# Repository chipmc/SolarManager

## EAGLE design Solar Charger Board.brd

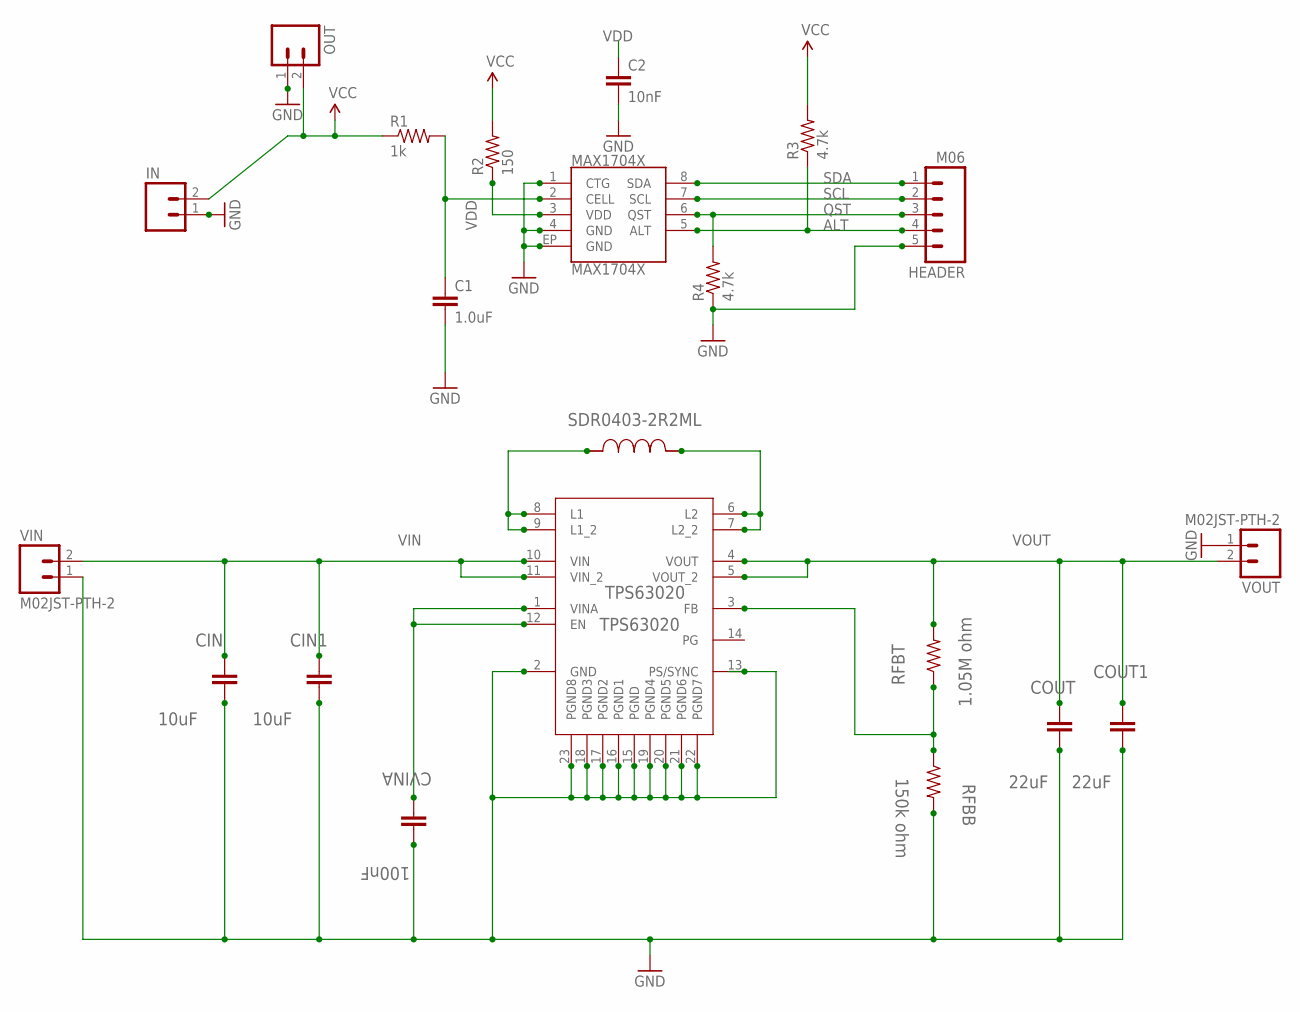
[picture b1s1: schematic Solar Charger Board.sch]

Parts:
C1: 1.0uF; 0805
C2: 10nF; 0805
CIN, CIN1: 10uF; 0805
COUT, COUT1: 22uF; 0805
CVINA: 100nF; 0805
HEADER: M06; 1X05
IN: input; JST-2-PTH
L1: SDR0403-2R2ML; SDR0403
MAX1704X: MAX1704X; TDFN-8
OUT: M02JST-PTH-2; JST-2-PTH
R1: 1k; 0805
R2: 150; 0805
R3, R4: 4.7k; 0805
RFBB: 150k ohm; 0805
RFBT: 1.05M ohm; 0805
TPS63020: TPS63020; QFN14-3X4MM
VIN: M02JST-PTH-2; JST-2-PTH
VOUT: M02JST-PTH-2; JST-2-PTH

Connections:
ALT: HEADER.4, MAX1704X.5 (ALT), R3.1
FB: RFBB.1, RFBT.1, TPS63020.3 (FB)
GND: C1.2, C2.2, CIN.2, CIN1.2, COUT.2, COUT1.2, CVINA.2, HEADER.5, IN.1, MAX1704X.1 (CTG), MAX1704X.4 (GND), MAX1704X.EP (GND), OUT.1, R4.1, RFBB.2, TPS63020.2 (GND), TPS63020.13 (PS/SYNC), TPS63020.15 (PGND), TPS63020.16 (PGND1), TPS63020.17 (PGND2), TPS63020.18 (PGND3), TPS63020.19 (PGND4), TPS63020.20 (PGND5), TPS63020.21 (PGND6), TPS63020.22 (PGND7), TPS63020.23 (PGND8), VIN.1, VOUT.1
unnamed: CVINA.1, TPS63020.1 (VINA), TPS63020.12 (EN)
unnamed: C1.1, MAX1704X.2 (CELL), R1.2
unnamed: L1.1, TPS63020.8 (L1), TPS63020.9 (L1_2)
unnamed: L1.2, TPS63020.6 (L2), TPS63020.7 (L2_2)
QST: HEADER.3, MAX1704X.6 (QST), R4.2
SCL: HEADER.2, MAX1704X.7 (SCL)
SDA: HEADER.1, MAX1704X.8 (SDA)
VCC: IN.2, OUT.2, R1.1, R2.2, R3.2
VDD: C2.1, MAX1704X.3 (VDD), R2.1
VIN: CIN.1, CIN1.1, TPS63020.10 (VIN), TPS63020.11 (VIN_2), VIN.2
VOUT: COUT.1, COUT1.1, RFBT.2, TPS63020.4 (VOUT), TPS63020.5 (VOUT_2), VOUT.2

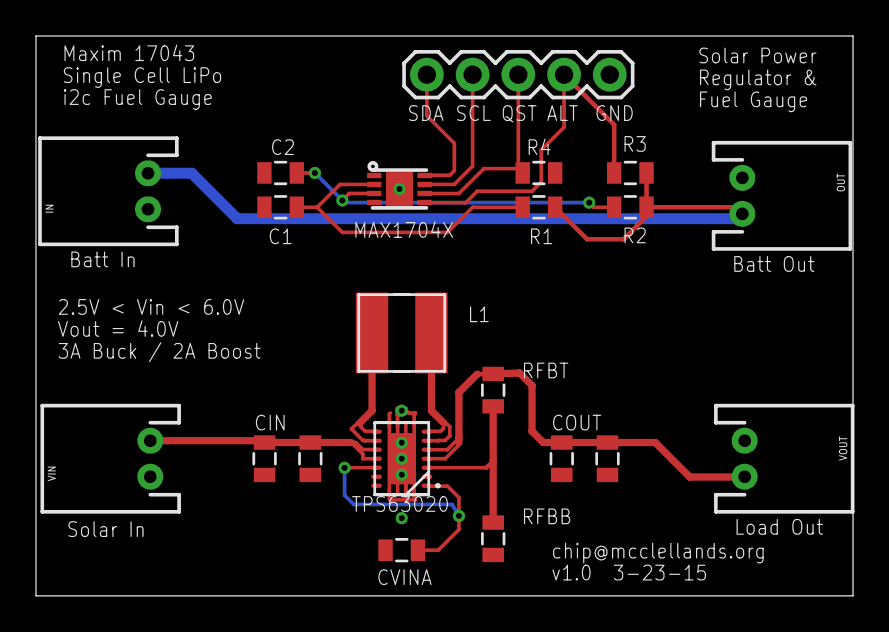
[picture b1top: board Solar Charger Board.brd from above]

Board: 2 copper layers, 45.4 x 31.1 mm, 21 parts (0 on the bottom side), 14 nets.

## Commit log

2015-05-11 EAGLE 7.0 Files for Solar Manager Board
    First Post

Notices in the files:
parts and their libraries:
SparkFun-Connectors: Licensing: Creative Commons ShareAlike 4.0 International - https://creativecommons.org/licenses/by-sa/4.0
